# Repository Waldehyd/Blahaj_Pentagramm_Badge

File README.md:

# Blahaj_Pentagramm_Badge

The Shorktagram-Badge features a beautiful PCB-Frontplate backed with 15 individually controllable LEDs, Temperature and Humidity Sensor as well as an optional Motion Sensor. This setup makes it ideal to be used as an air sensor by day and a nightlight by uh... night.

IBOM:
https://htmlpreview.github.io/?https://github.com/Waldehyd/Blahaj_Pentagramm_Badge/blob/main/IBOM/ibom.html

Firmware:

Build WLED (https://github.com/Aircoookie/WLED) using PlatformIO with the following Environment using the Buildflags for BME280 and PIR:

```
[env:d1_mini]
...
build_flags = ${common.build_flags_esp8266} -D USERMOD_BME280 -D USERMOD_PIRSWITCH -D PIR_SENSOR_PIN=13
...
```

Configuration:
```
LED Preferences: 
    -> Length = 15
    -> GPIO = 14
Usermods:
    -> SDA = 4
    -> SCL = 5
    -> Enabled

    Reboot
```

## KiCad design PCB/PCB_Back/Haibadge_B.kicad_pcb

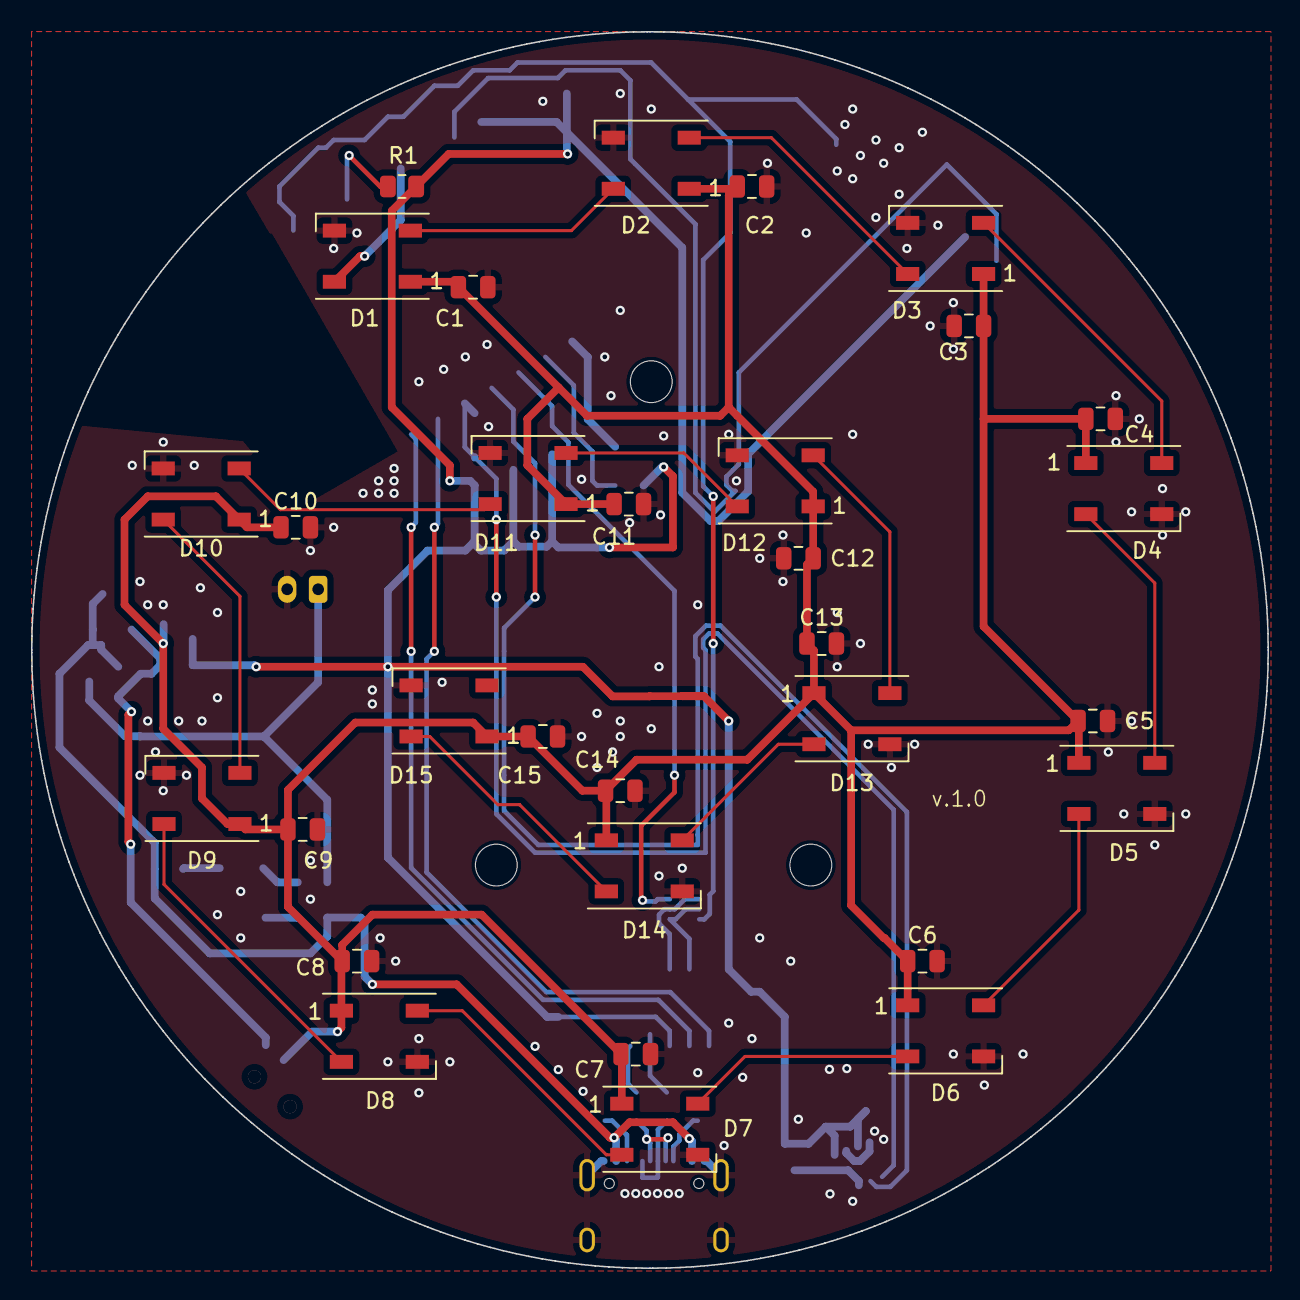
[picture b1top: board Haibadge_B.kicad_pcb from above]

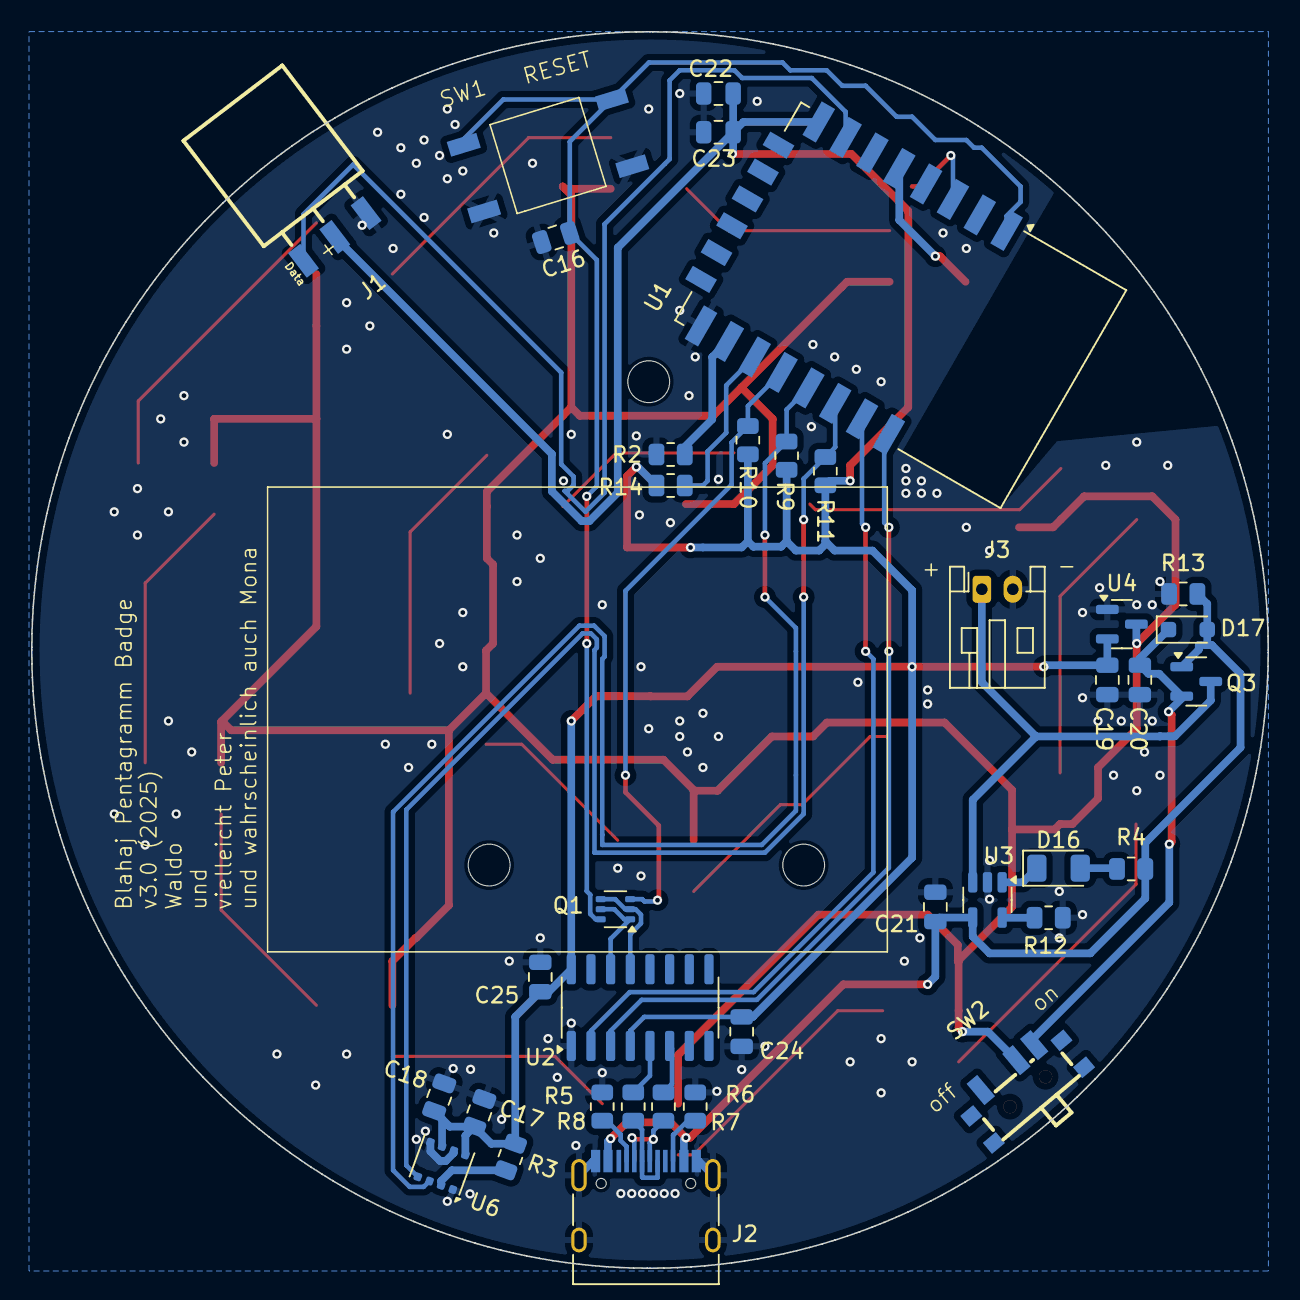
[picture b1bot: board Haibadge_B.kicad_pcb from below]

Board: 2 copper layers, 79.8 x 79.8 mm, 71 parts (37 on the bottom side), 43 nets.

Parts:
C1, C2, C3, C4, C5, C6, C7, C8, C9, C10, C11, C12, C13, C14, C15, C16, C17, C18, C22, C24, C25: 100nF; C_0805_2012Metric
C19, C20, C23: 1uF; C_0805_2012Metric
C21: 4.7uF; C_0805_2012Metric
D1, D2, D3, D4, D5, D6, D7, D8, D9, D10, D11, D12, D13, D14, D15: WS2812B; LED_WS2812B_PLCC4_5.0x5.0mm_P3.2mm
D16: LED; LED_1206_3216Metric
D17: D; D_SOD-323_HandSoldering
H1, H2, H3: MountingHole; MountingHole_2.7mm_M2.5
J1: Sensor connector; HDR-SMD_3P-P2.54-H-F-L11.5
J2: USB_C_Receptacle_USB2.0; USB_C_Receptacle_HRO_TYPE-C-31-M-12
J3: Lipo connector; JST_PH_S2B-PH-K_1x02_P2.00mm_Horizontal
Q1: UMH3N; SOT-363_SC-70-6
Q3: Q_PMOS_GSD; SOT-23
R1, R2, R3, R9, R10, R11, R13, R14: 10k; R_0805_2012Metric
R4, R12: 2k; R_0805_2012Metric
R5, R6: 5k1; R_0805_2012Metric
R7, R8: 22; R_0805_2012Metric
SW1: SW_Push_Dual; KH-6X6X6H-STM
SW2: SW_PWR; SW-SMD_MK-12C02-G025
U1: ESP-12E
U2: CH340C; SOIC-16_3.9x9.9mm_P1.27mm
U3: MCP73831-2-OT; SOT-23-5
U4: MCP1700x-330xxTT; SOT-23
U6: BME680; Bosch_LGA-8_3x3mm_P0.8mm_ClockwisePinNumbering

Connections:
+3V3: C17.1, C18.1, C19.1, C22.1, C23.1, C24.1, C25.1, J1.2, R1.1, R3.2, R9.2, R10.2, R11.2, R14.2, U1.8 (VCC), U2.4 (V3), U2.16 (VCC), U4.2 (VO), U6.6 (VDDIO), U6.8 (VDD)
+5V: C21.1, D17.2 (A), J2.A4 (VBUS), J2.A9 (VBUS), J2.B4 (VBUS), J2.B9 (VBUS), Q3.1 (G), R4.2, R13.2, U3.4 (V_{DD})
+BATT: J3.1, Q3.3 (D), U3.3 (V_{BAT})
/WS2812B/WS2812B: D1.4 (DIN), U1.5 (GPIO14)
/uC/D+: J2.A6 (D+), J2.B6 (D+), R8.2
/uC/D-: J2.A7 (D-), J2.B7 (D-), R7.1
/uC/RD+: R8.1, U2.5 (UD+)
/uC/RD-: R7.2, U2.6 (UD-)
DTR: Q1.2 (B1), Q1.4 (E2), U2.13 (~DTR)
GND: C1.2, C2.2, C3.2, C4.2, C5.2, C6.2, C7.2, C8.2, C9.2, C10.2, C11.2, C12.2, C13.2, C14.2, C15.2, C16.2, C17.2, C18.2, C19.2, C20.2, C21.2, C22.2, C23.2, C24.2, C25.2, D1.3 (VSS), D2.3 (VSS), D3.3 (VSS), D4.3 (VSS), D5.3 (VSS), D6.3 (VSS), D7.3 (VSS), D8.3 (VSS), D9.3 (VSS), D10.3 (VSS), D11.3 (VSS), D12.3 (VSS), D13.3 (VSS), D14.3 (VSS), D15.3 (VSS), J1.1, J2.A1 (GND), J2.A12 (GND), J2.B1 (GND), J2.B12 (GND), J2.S1 (SHIELD), J3.2, R2.2, R5.2, R6.1, R12.1, R13.1, SW1.3, SW1.4, U1.15 (GND), U2.1 (GND), U3.2 (V_{SS}), U4.1 (GND), U6.1 (GND), U6.5 (SDO), U6.7 (GND)
GPIO0: Q1.3 (C2), R10.1, U1.18 (GPIO0)
unnamed: D1.2 (DOUT), D2.4 (DIN)
unnamed: D2.2 (DOUT), D3.4 (DIN)
unnamed: D3.2 (DOUT), D4.4 (DIN)
unnamed: D4.2 (DOUT), D5.4 (DIN)
unnamed: D5.2 (DOUT), D6.4 (DIN)
unnamed: D6.2 (DOUT), D7.4 (DIN)
unnamed: D7.2 (DOUT), D8.4 (DIN)
unnamed: D8.2 (DOUT), D9.4 (DIN)
unnamed: D9.2 (DOUT), D10.4 (DIN)
unnamed: D10.2 (DOUT), D11.4 (DIN)
unnamed: D11.2 (DOUT), D12.4 (DIN)
unnamed: D12.2 (DOUT), D13.4 (DIN)
unnamed: D13.2 (DOUT), D14.4 (DIN)
unnamed: D14.2 (DOUT), D15.4 (DIN)
unnamed: D16.2 (A), R4.1
unnamed: D16.1 (K), U3.1 (STAT)
unnamed: C20.1, D17.1 (K), Q3.2 (S), SW2.3 (C)
unnamed: J2.A5 (CC1), R5.1
unnamed: J2.B5 (CC2), R6.2
unnamed: R1.2, U1.3 (EN)
unnamed: U1.22 (GPIO1/TXD), U2.3 (RXD)
unnamed: R14.1, U1.17 (GPIO2)
unnamed: U1.21 (GPIO3/RXD), U2.2 (TXD)
unnamed: R9.1, U1.19 (GPIO4), U6.3 (SDI)
unnamed: R11.1, U1.20 (GPIO5), U6.4 (SCK)
unnamed: R2.1, U1.16 (GPIO15)
unnamed: R12.2, U3.5 (PROG)
unnamed: R3.1, U6.2 (CSB)
RST: C16.1, Q1.6 (C1), SW1.1, SW1.2, U1.1 (~RST)
RTS: Q1.1 (E1), Q1.5 (B2), U2.14 (~RTS)
Sensor: J1.3, U1.7 (GPIO13)
VCC: C1.1, C2.1, C3.1, C4.1, C5.1, C6.1, C7.1, C8.1, C9.1, C10.1, C11.1, C12.1, C13.1, C14.1, C15.1, D1.1 (VDD), D2.1 (VDD), D3.1 (VDD), D4.1 (VDD), D5.1 (VDD), D6.1 (VDD), D7.1 (VDD), D8.1 (VDD), D9.1 (VDD), D10.1 (VDD), D11.1 (VDD), D12.1 (VDD), D13.1 (VDD), D14.1 (VDD), D15.1 (VDD), SW2.2 (B), U4.3 (VI)

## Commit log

2025-03-22 Increased Thickness for Velcro, minor changes
2025-05-11 Updated WLED Buildsettings for v15
2025-07-15 Added SDA/SCL Buildflags, Init Manual
2025-08-01 Update Case to latest (Mounting Plate, Hook)
2025-08-22 Add current state of SetupGuide
2025-08-23 Update Docs
2025-08-23 More Guide updates
2025-08-24 Work on SetupGuide
2025-08-24 Render latest
2025-08-26 Update Case and STL (not correclty orientated yet)
2025-08-28 Added default WLED Templates for easy flashing
2025-08-28 Readded PIR
2025-08-28 Rename Folder
2025-08-29 New IBOM version, put rendered IBOM into root directory
2025-08-29 Fixed Link to IBOMM render
2025-09-01 Update with correct STL sizes and rotations, added Stand
2025-09-02 Add a Multiboard compatible mount
